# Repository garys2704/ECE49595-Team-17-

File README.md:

# ECE49595 Senior Design - Team E17

## Samantha Gary, Adam Mack, Michael Huang, Matthew Mozingo

The wearable sound alert system is designed to alert the user to surrounding sounds and their corresponding intensities. The product will be worn around the chest and the microphones surrounding the device will take sound input and depending on the direction the sound is coming from, it will vibrate in that area on the device. Our device is designed with deaf people and people who suffer from hearing loss in mind, to give them a better awareness of their surroundings.

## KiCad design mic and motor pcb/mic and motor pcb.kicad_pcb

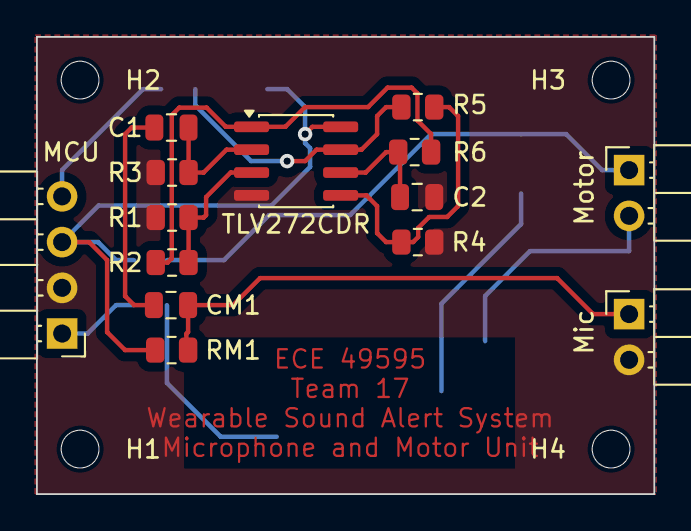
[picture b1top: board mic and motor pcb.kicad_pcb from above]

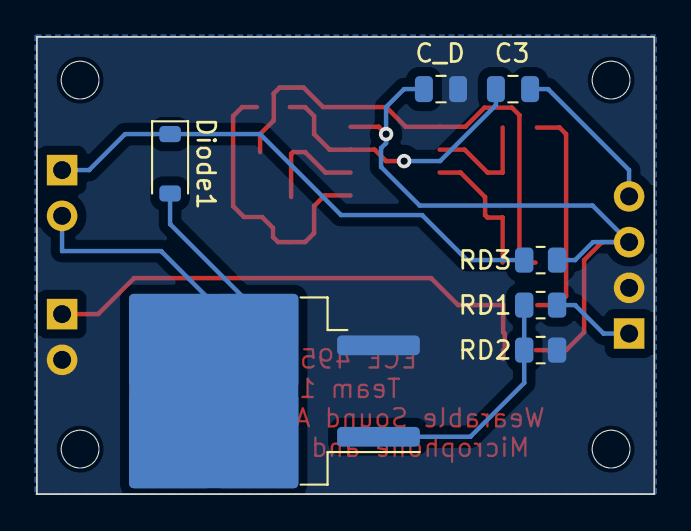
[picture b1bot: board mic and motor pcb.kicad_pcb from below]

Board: 2 copper layers, 34.3 x 25.4 mm, 25 parts (7 on the bottom side), 15 nets.

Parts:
C1: 4.7u; C_0805_2012Metric
C2: 0.1u; C_0805_2012Metric
C3: 0.01u; C_0805_2012Metric
CM1: C_Small; C_0805_2012Metric
C_D: C_Small; C_0805_2012Metric
Diode1: 1N5819; D_SOD-123
H1, H2, H3, H4: MountingHole; MountingHole_2.1mm
MCU: Conn_01x04_Pin; PinHeader_1x04_P2.54mm_Horizontal
Mic: Conn_01x02_Pin; PinHeader_1x02_P2.54mm_Horizontal
Motor: Conn_01x02_Pin; PinHeader_1x02_P2.54mm_Horizontal
Q1: IRLZ34N; TO-263-2
R1: 2.2k; R_0805_2012Metric
R2: 3.3k; R_0805_2012Metric
R3: 330; R_0805_2012Metric
R4, R6: 390; R_0805_2012Metric
R5: 4.7k; R_0805_2012Metric
RD1: 1k; R_0805_2012Metric
RD2: 10k; R_0805_2012Metric
RD3: 10; R_0805_2012Metric
RM1: 2.2k; R_0805_2012Metric
U2: TLV272CDR; SOIC-8_3.9x4.9mm_P1.27mm

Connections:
/Amp_out: C3.2, MCU.4
/Mic_pwr: CM1.2, Mic.1, RM1.2
/MotorPWMinput: MCU.1, RD1.1
/Motor_drain: Diode1.2 (A), Motor.2, Q1.2 (D)
/Motor_pwr: Diode1.1 (K), Motor.1, RD3.1
GND: C2.1, C_D.1, MCU.2, Mic.2, Q1.3 (S), R1.2, R3.2, R4.2, RD2.2, U2.4 (V-)
unnamed: C1.1, CM1.1
unnamed: C3.1, R5.1, U2.7
unnamed: Q1.1 (G), RD1.2, RD2.1
unnamed: R2.1, R6.2, U2.1
unnamed: R1.1, R2.2, U2.3 (+)
unnamed: C1.2, R3.1, U2.2 (-)
unnamed: R4.1, R5.2, U2.5 (+)
unnamed: C2.2, R6.1, U2.6 (-)
VCC: C_D.2, MCU.3, RD3.2, RM1.1, U2.8 (V+)

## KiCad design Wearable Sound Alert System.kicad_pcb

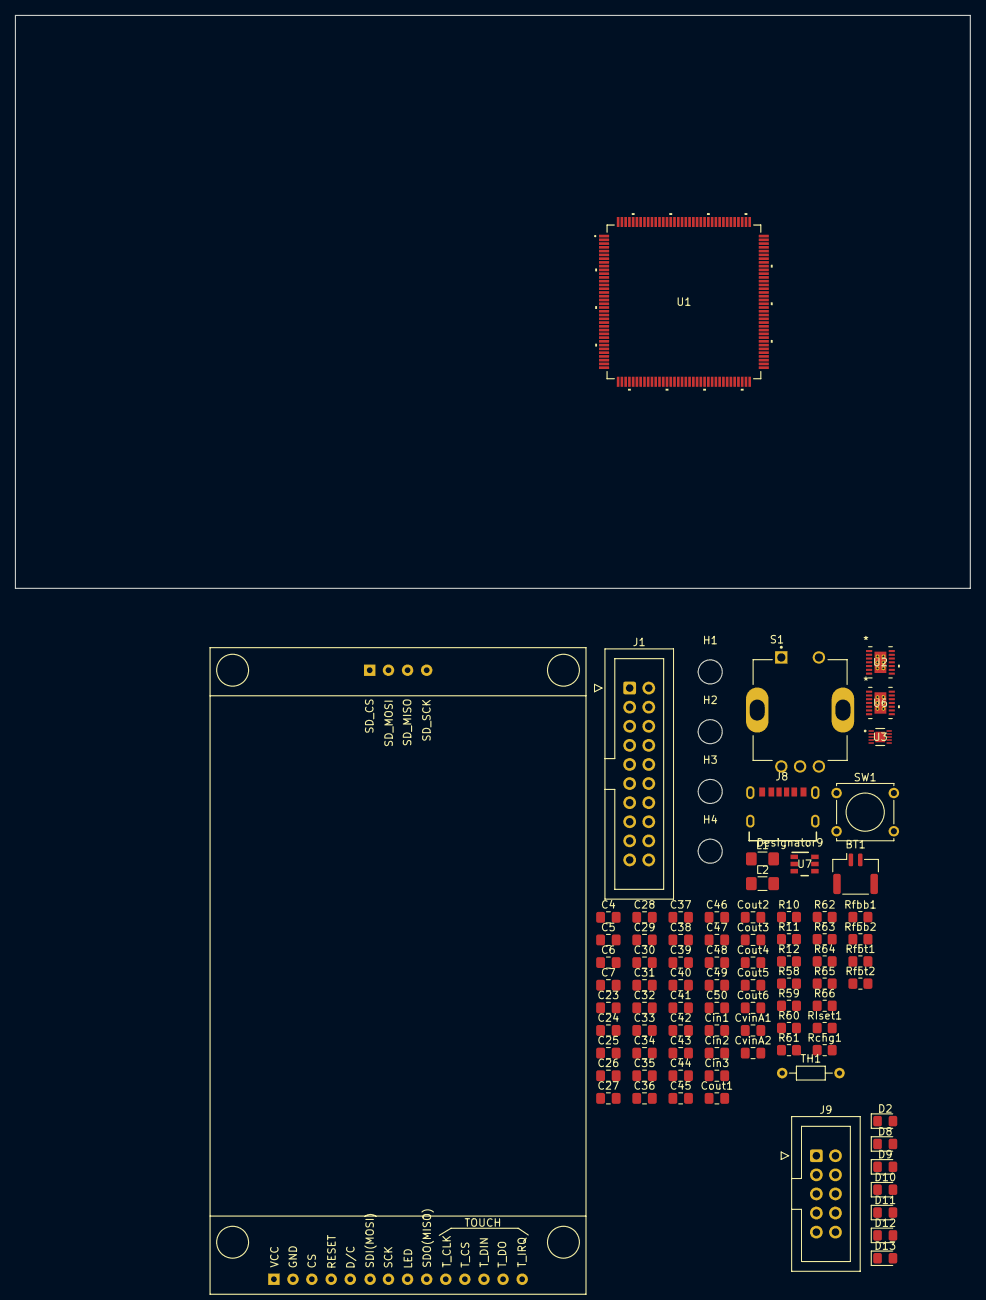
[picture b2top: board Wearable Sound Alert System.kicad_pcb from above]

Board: 2 copper layers, 127.0 x 76.2 mm, 87 parts (0 on the bottom side), 64 nets, no tracks yet.

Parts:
BT1: Battery_Cell; Molex_CLIK-Mate_502386-0270_1x02-1MP_P1.25mm_Horizontal
C4, C50: 0.1u; C_0805_2012Metric_Pad1.18x1.45mm_HandSolder
C5: 0.47p; C_0805_2012Metric_Pad1.18x1.45mm_HandSolder
C6, C7, C26, C49: 1u; C_0805_2012Metric_Pad1.18x1.45mm_HandSolder
C23, C24: 2.2u; C_0805_2012Metric_Pad1.18x1.45mm_HandSolder
C25, C27, C28, C29, C30, C31, C32, C33, C34, C35, C36, C37, C38, C39, C40, C42, C43, C44, C45, C46, C47, C48: 100n; C_0805_2012Metric_Pad1.18x1.45mm_HandSolder
C41: 4.7u; C_0805_2012Metric_Pad1.18x1.45mm_HandSolder
Cin1, Cin3: 10u; C_0805_2012Metric_Pad1.18x1.45mm_HandSolder
Cin2: 22u; C_0805_2012Metric_Pad1.18x1.45mm_HandSolder
Cout1, Cout2, Cout3, Cout4, Cout5, Cout6: 10u; C_0805_2012Metric_Pad1.18x1.45mm_HandSolder
CvinA1, CvinA2: 100n; C_0805_2012Metric_Pad1.18x1.45mm_HandSolder
D2: HB_CHG; LED_0805_2012Metric_Pad1.15x1.40mm_HandSolder
D8: HB1; LED_0805_2012Metric_Pad1.15x1.40mm_HandSolder
D9: HB2; LED_0805_2012Metric_Pad1.15x1.40mm_HandSolder
D10: HB3; LED_0805_2012Metric_Pad1.15x1.40mm_HandSolder
D11: DB1; LED_0805_2012Metric_Pad1.15x1.40mm_HandSolder
D12: DB2; LED_0805_2012Metric_Pad1.15x1.40mm_HandSolder
D13: HB4; LED_0805_2012Metric_Pad1.15x1.40mm_HandSolder
H1, H2, H3, H4: MountingHole; MountingHole_3.2mm_M3
J1: ST-LINK Connector; IDC-Header_2x10_P2.54mm_Vertical
J8: USB4125-GF-A_REVA2; GCT_USB4125-GF-A_REVA2
J9: Extra GPIO Header; IDC-Header_2x05_P2.54mm_Vertical
L1: 1u; L_1206_3216Metric_Pad1.42x1.75mm_HandSolder
L2: 1.3u; L_1206_3216Metric_Pad1.42x1.75mm_HandSolder
R10: 10m; R_0805_2012Metric_Pad1.20x1.40mm_HandSolder
R11, R12: 5.1k; R_0805_2012Metric_Pad1.20x1.40mm_HandSolder
R58: 10k; R_0805_2012Metric_Pad1.20x1.40mm_HandSolder
R59, R60: 100k; R_0805_2012Metric_Pad1.20x1.40mm_HandSolder
R61, R62, R63, R64, R65, R66: 1k; R_0805_2012Metric_Pad1.20x1.40mm_HandSolder
RIset1: 910; R_0805_2012Metric_Pad1.20x1.40mm_HandSolder
Rchg1: 1.5k; R_0805_2012Metric_Pad1.20x1.40mm_HandSolder
Rfbb1, Rfbb2: 137k; R_0805_2012Metric_Pad1.20x1.40mm_HandSolder
Rfbt1, Rfbt2: 768k; R_0805_2012Metric_Pad1.20x1.40mm_HandSolder
S1: PEC11R-4220F-S0024; XDCR_PEC11R-4220F-S0024
SW1: SW_Push; SW_Tactile_Straight_KSA0Axx1LFTR
TH1: Thermistor; R_Axial_DIN0204_L3.6mm_D1.6mm_P7.62mm_Horizontal
U1: STM32F767ZIT6; LQFP144-20x20mm_STM
U2, U6: TPS63020DSJR
U3: MAX17055ETB+T; MAX17055
U4: 2.8_240x320_touch_sd_spi; 2.8_tft_240x320_touch_sd_spi
U7: BQ21040DBVR; DBV0006A_N

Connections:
3.3V_0.5A: Cout3.1, R62.2, Rfbt1.1, U2.4 (VOUT)
3.3V_0.6A: C25.1, C26.1, C27.1, C28.1, C29.1, C30.1, C31.1, C32.1, C33.1, C34.1, C35.1, C36.1, C37.1, C38.1, C39.1, C40.1, C41.1, C42.1, C43.1, C44.1, C45.1, C46.1, C47.1, C48.1, C49.1, Cout6.1, R58.1, R60.1, R61.1, Rfbt2.1, S1.C (COM), U1.6 (VBAT), U1.17 (VDD), U1.30 (VDD), U1.32 (VREF+), U1.33 (VDDA), U1.39 (VDD), U1.52 (VDD), U1.62 (VDD), U1.72 (VDD), U1.84 (VDD), U1.108 (VDD), U1.131 (VDD), U1.144 (VDD), U4.1 (VCC), U4.8 (LED), U6.4 (VOUT)
5V_In: C6.1, J8.A9 (VBUS), R63.2, U7.6 (IN)
Batt_ALRT: U1.29 (PC3), U3.8 (ALRT)
Batt_SCL: U1.44 (PC4), U3.3 (SCL)
Batt_SDA: U1.45 (PC5), U3.4 (SDA)
ENC_CLK: S1.A, U1.42 (PA6)
ENC_DT: S1.B, U1.97 (PC7)
ENC_SW: R59.2, S1.2, U1.43 (PA7)
GND: C4.2, C6.2, C7.1, C23.1, C24.2, C25.2, C26.2, C27.2, C28.2, C29.2, C30.2, C31.2, C32.2, C33.2, C34.2, C35.2, C36.2, C37.2, C38.2, C39.2, C40.2, C41.2, C42.2, C43.2, C44.2, C45.2, C46.2, C47.2, C48.2, C49.2, C50.2, Cin1.2, Cin2.2, Cout2.2, Cout5.2, CvinA1.2, CvinA2.2, D8.1 (K), D9.1 (K), D10.1 (K), D11.1 (K), D12.1 (K), D13.1 (K), J1.4, J1.6, J1.8, J1.10, J1.12, J1.14, J1.16, J1.18, J1.20, J8.A12 (GND), J8.B12 (GND__1), J8.S1 (SHIELD), J8.S2 (SHIELD__1), J8.S3 (SHIELD__2), J8.S4 (SHIELD__3), R10.2, R11.2, R12.2, R59.1, RIset1.2, Rfbb1.2, Rfbb2.2, S1.SH1 (SHIELD), S1.SH2 (SHIELD__1), SW1.1, TH1.2, U1.16 (VSS), U1.31 (VSSA), U1.38 (VSS), U1.51 (VSS), U1.61 (VSS), U1.83 (VSS), U1.94 (VSS), U1.107 (VSS), U1.120 (VSS), U1.130 (VSS), U2.2 (GND), U2.13 (PS/SYNC), U3.5 (CSN), U4.2 (GND), U6.2 (GND), U6.13 (PS/SYNC), U7.5 (VSS)
LCD_CLK: U1.41 (PA5), U4.7 (SCK)
LCD_CS: U1.136 (PB6), U4.3 (CS)
LCD_D/C: U1.27 (PC1), U4.5 (D/C)
LCD_MISO: U1.139 (PB8), U4.9 (SDO(MISO))
LCD_MOSI: U1.137 (PB7), U4.6 (SDI(MOSI))
LCD_RST: U1.140 (PB9), U4.4 (RESET)
NRST: C50.1, J1.15, R60.2, SW1.2, U1.25 (NRST)
unnamed: Cin1.1, Cin3.2
unnamed: Cout1.1, Cout6.2
unnamed: Cout1.2, Cout2.1
unnamed: Cout3.2, Cout4.1
unnamed: Cout4.2, Cout5.1
unnamed: D2.2 (A), Rchg1.2
unnamed: D2.1 (K), U7.3 (CHG_N)
unnamed: D8.2 (A), R61.2
unnamed: D9.2 (A), R62.1
unnamed: D10.2 (A), R63.1
unnamed: D11.2 (A), R64.2
unnamed: D12.2 (A), R65.2
unnamed: D13.2 (A), R66.1
unnamed: J8.A5 (CC1), R11.1
unnamed: J8.B5 (CC2), R12.1
unnamed: L1.1, U6.6 (L2)
unnamed: L1.2, U6.8 (L1)
unnamed: L2.1, U2.6 (L2)
unnamed: L2.2, U2.8 (L1)
unnamed: R58.2, S1.1
unnamed: R64.1, U1.114 (PD0)
unnamed: R65.1, U1.115 (PD1)
unnamed: C23.2, C24.1, U1.71 (VCAP_1), U1.106 (VCAP_2)
unnamed: CvinA1.1, U2.1 (VINA), U2.12 (EN)
unnamed: Rfbb1.1, Rfbt1.2, U2.3 (FB)
unnamed: C5.1, U3.7 (REG)
unnamed: CvinA2.1, U6.1 (VINA), U6.12 (EN)
unnamed: Rfbb2.1, Rfbt2.2, U6.3 (FB)
unnamed: RIset1.1, U7.4 (ISET)
unnamed: TH1.1, U7.1 (TS)
PE0: J9.1, U1.141 (PE0)
PE1: J9.2, U1.142 (PE1)
PE2: J9.3, U1.1 (PE2)
PE3: J9.4, U1.2 (PE3)
PE4: J9.5, U1.3 (PE4)
PE5: J9.6, U1.4 (PE5)
PE6: J9.7, U1.5 (PE6)
PE7: J9.8, U1.58 (PE7)
PE8: J9.9, U1.59 (PE8)
PE9: J9.10, U1.60 (PE9)
SWCLK: J1.9, U1.109 (PA14)
SWDIO: J1.7, U1.105 (PA13)
SWO: J1.13, U1.133 (PB3)
TDI: J1.5, U1.110 (PA15)
TRST: J1.3, U1.134 (PB4)
V_Batt+: BT1.1 (+), C4.1, C7.2, Cin2.1, Cin3.1, R66.2, Rchg1.1, U2.10 (VIN), U3.10 (BATT), U6.10 (VIN), U7.2 (OUT)
V_Batt-: BT1.2 (-), C5.2, R10.1, U3.6 (CSP)

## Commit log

2025-12-03 Analog Mic directional test
2026-01-20 Added initial PCB schematic
    Looked into what components have existing symbols and/or footprints in KiCad
2026-01-28 Update main.cpp for four mic testing
2026-02-10 Uploading current PCB schematics
    1. split the mic-motor pairs off of main board
    2. main board has footprints assigned, PCB is started, but no layout work has been done
    3. Uploaded downloaded footprints used, I can upload the symbols later
2026-02-14 Added updated schematic
    Includes BOM, new footprints
2026-02-16 Update main.cpp (back to two mic system)
2026-02-18 Updated with TDOA algorithm
2026-02-18 TDOA test with 4 mics
2026-02-19 Archive of Revision A
    This is the 'finalized' version of the schematic before I remove one of the buck-boost converters to implement the boost converter on the mic/motor boards
2026-02-19 Amplifier and boost converter kicad
2026-02-19 Mic and motor pcb
2026-02-24 Update tdoa_4mics.cpp
    updated with auto centering
2026-03-04 Revision D Archive upload
    Same as submitted design for reviewing, but has level shifter and boost converter added to board!
2026-03-24 Create User Interface
    Code for the buttons, rotary encoder, and ili9341 display.
2026-03-25 Uploaded UI MCU .c/.h files
2026-03-27 Defined TFT dimensions in GFX file
2026-03-27 Updated Graphics functions in GFX
    Added functions for menu and battery bar display.
2026-03-27 Removed Redundant functions
2026-03-27 Add new functions for menu and battery
2026-03-27 Fixed definition
2026-03-31 Uploading current revision of PCB
    I'm uploading this to allow us to open the design on the big desktop for visibility
2026-03-31 Uploading current mic and motor PCB design
2026-04-07 Added Battery Management System
2026-04-14 upload
